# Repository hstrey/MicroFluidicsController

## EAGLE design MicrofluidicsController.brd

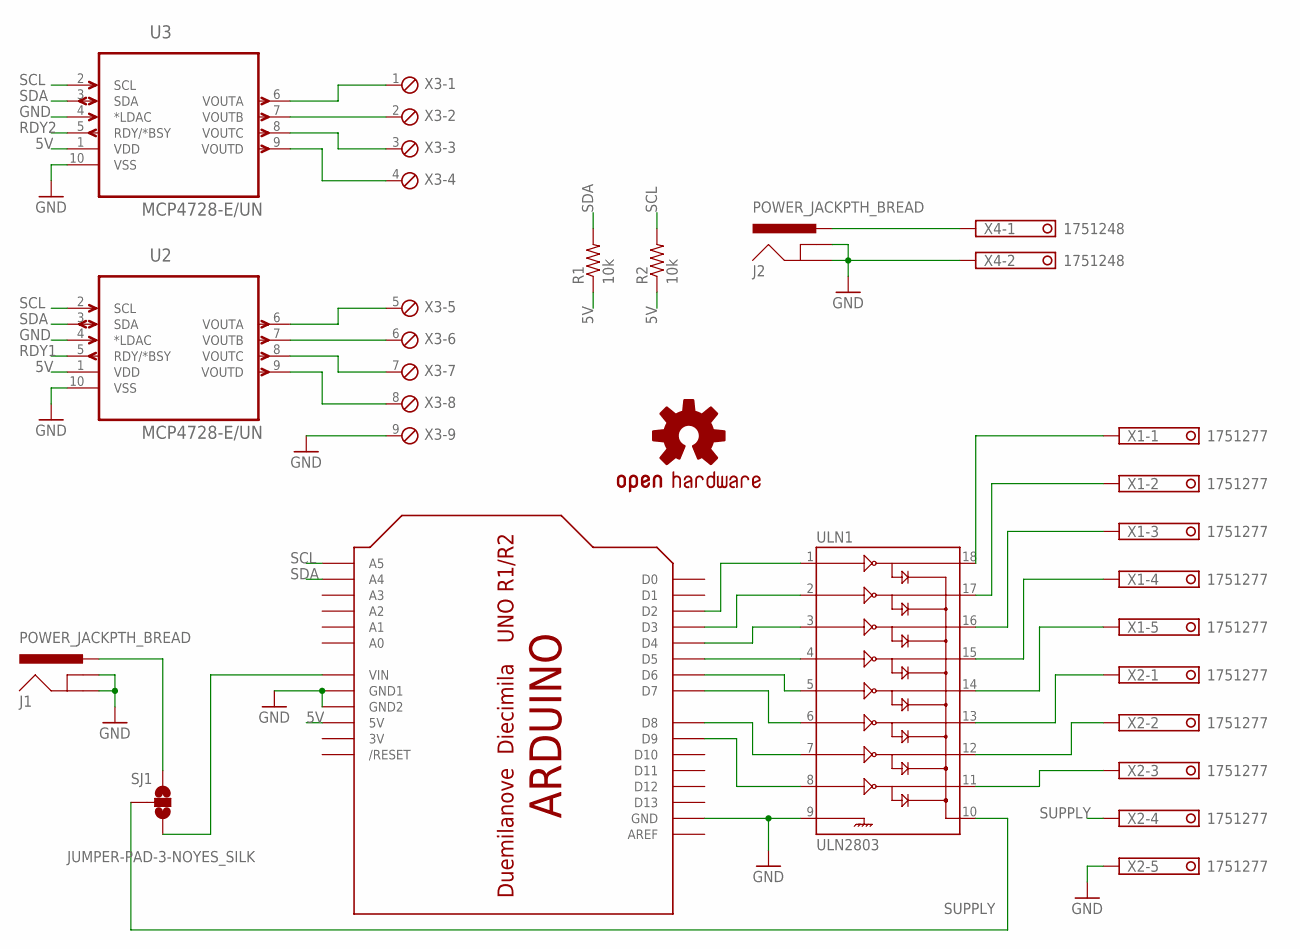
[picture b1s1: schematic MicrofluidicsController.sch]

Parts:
J1, J2: POWER_JACKPTH_BREAD; POWER_JACK_PTH_BREAD
LOGO1: OSHW-LOGOL; OSHW-LOGO-L
R1, R2: 10k; 0603-RES
SJ1: JUMPER-PAD-3-NOYES_SILK; PAD-JUMPER-3-NO_YES_SILK
U2, U3: MCP4728-E/UN; SOP50P490X110-10N
U$1: ARDUINOUNO; ARDUINO
ULN1: ULN2803; DIL18
X1, X2: 1751277
X3: MPT9; 9POL254
X4: 1751248

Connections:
3V: U$1.3V
5V: R1.1, R2.1, U2.1 (VDD), U3.1 (VDD), U$1.5V
GND: J1.GND, J1.GNDBREAK, J2.GND, J2.GNDBREAK, U2.4 (*LDAC), U2.10 (VSS), U3.4 (*LDAC), U3.10 (VSS), U$1.GND, U$1.GND1, U$1.GND2, ULN1.9, X2.5, X3.9, X4.2
unnamed: SJ1.3, U$1.VIN
unnamed: U$1.D2, ULN1.1
unnamed: U$1.D3, ULN1.2
unnamed: U$1.D4, ULN1.3
unnamed: U$1.D5, ULN1.4
unnamed: U$1.D6, ULN1.5
unnamed: U$1.D7, ULN1.6
unnamed: U$1.D8, ULN1.7
unnamed: U$1.D9, ULN1.8
unnamed: J1.PWR, SJ1.1
unnamed: ULN1.18, X1.1
unnamed: ULN1.17, X1.2
unnamed: ULN1.16, X1.3
unnamed: ULN1.15, X1.4
unnamed: ULN1.14, X1.5
unnamed: ULN1.13, X2.1
unnamed: ULN1.12, X2.2
unnamed: ULN1.11, X2.3
unnamed: U2.6 (VOUTA), X3.5
unnamed: U2.7 (VOUTB), X3.6
unnamed: U2.8 (VOUTC), X3.7
unnamed: U2.9 (VOUTD), X3.8
unnamed: U3.6 (VOUTA), X3.1
unnamed: U3.7 (VOUTB), X3.2
unnamed: U3.8 (VOUTC), X3.3
unnamed: U3.9 (VOUTD), X3.4
unnamed: J2.PWR, X4.1
RDY1: U2.5 (RDY/*BSY)
RDY2: U3.5 (RDY/*BSY)
SCL: R2.2, U2.2 (SCL), U3.2 (SCL), U$1.A5
SDA: R1.2, U2.3 (SDA), U3.3 (SDA), U$1.A4
SUPPLY: SJ1.2, ULN1.10, X2.4

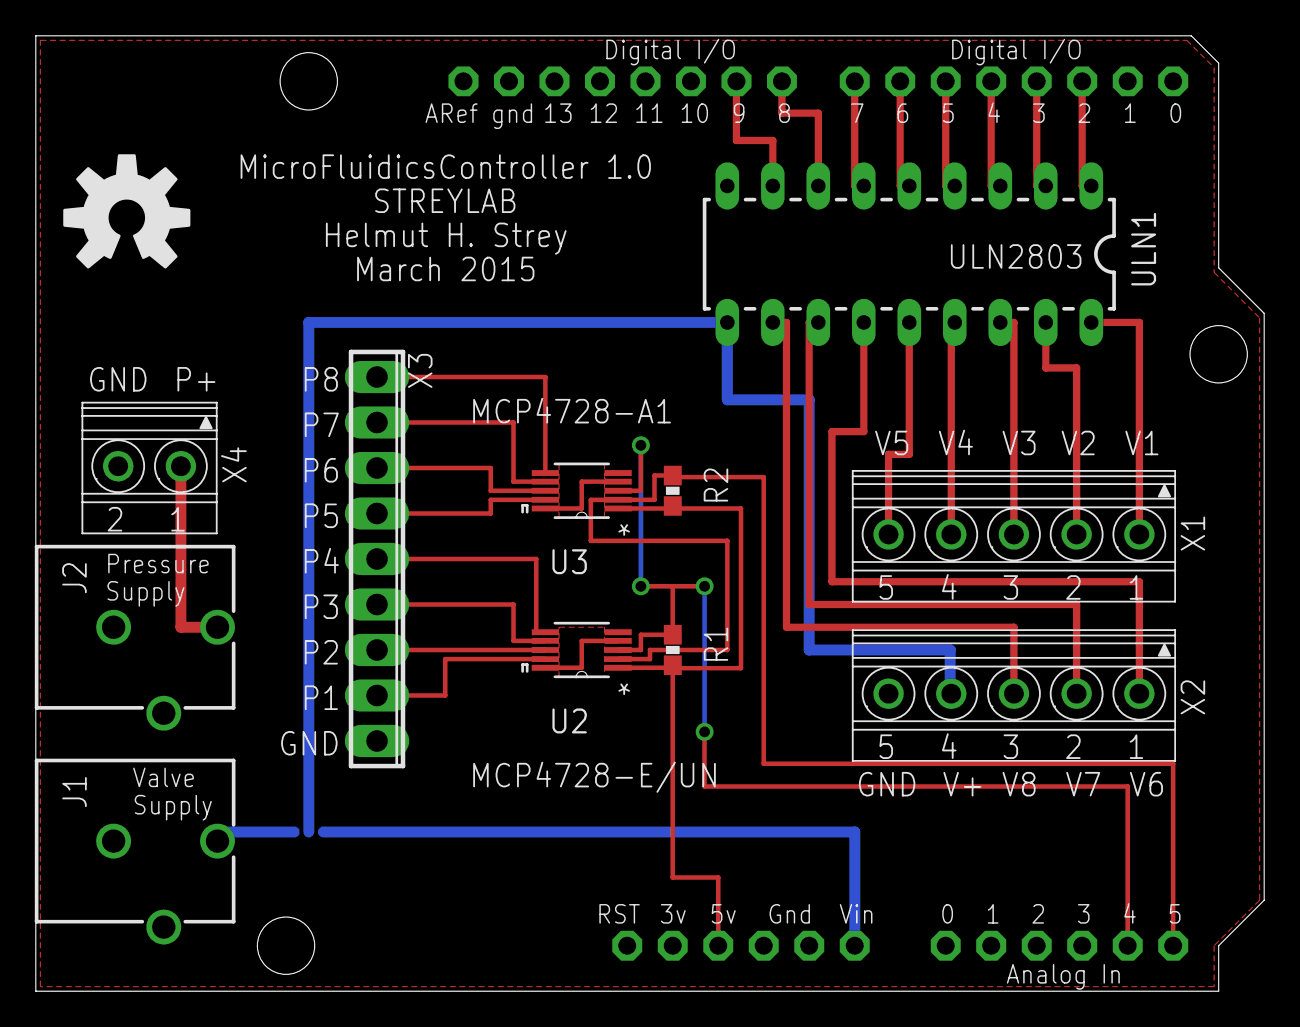
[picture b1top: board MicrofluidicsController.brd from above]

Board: 2 copper layers, 68.6 x 53.3 mm, 14 parts (1 on the bottom side), 32 nets.

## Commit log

2015-04-08 board + schematic
2015-04-14 added Arduino sketch

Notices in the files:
parts and their libraries:
SparkFun-Connectors: Licensing: Creative Commons ShareAlike 4.0 International - https://creativecommons.org/licenses/by-sa/4.0
